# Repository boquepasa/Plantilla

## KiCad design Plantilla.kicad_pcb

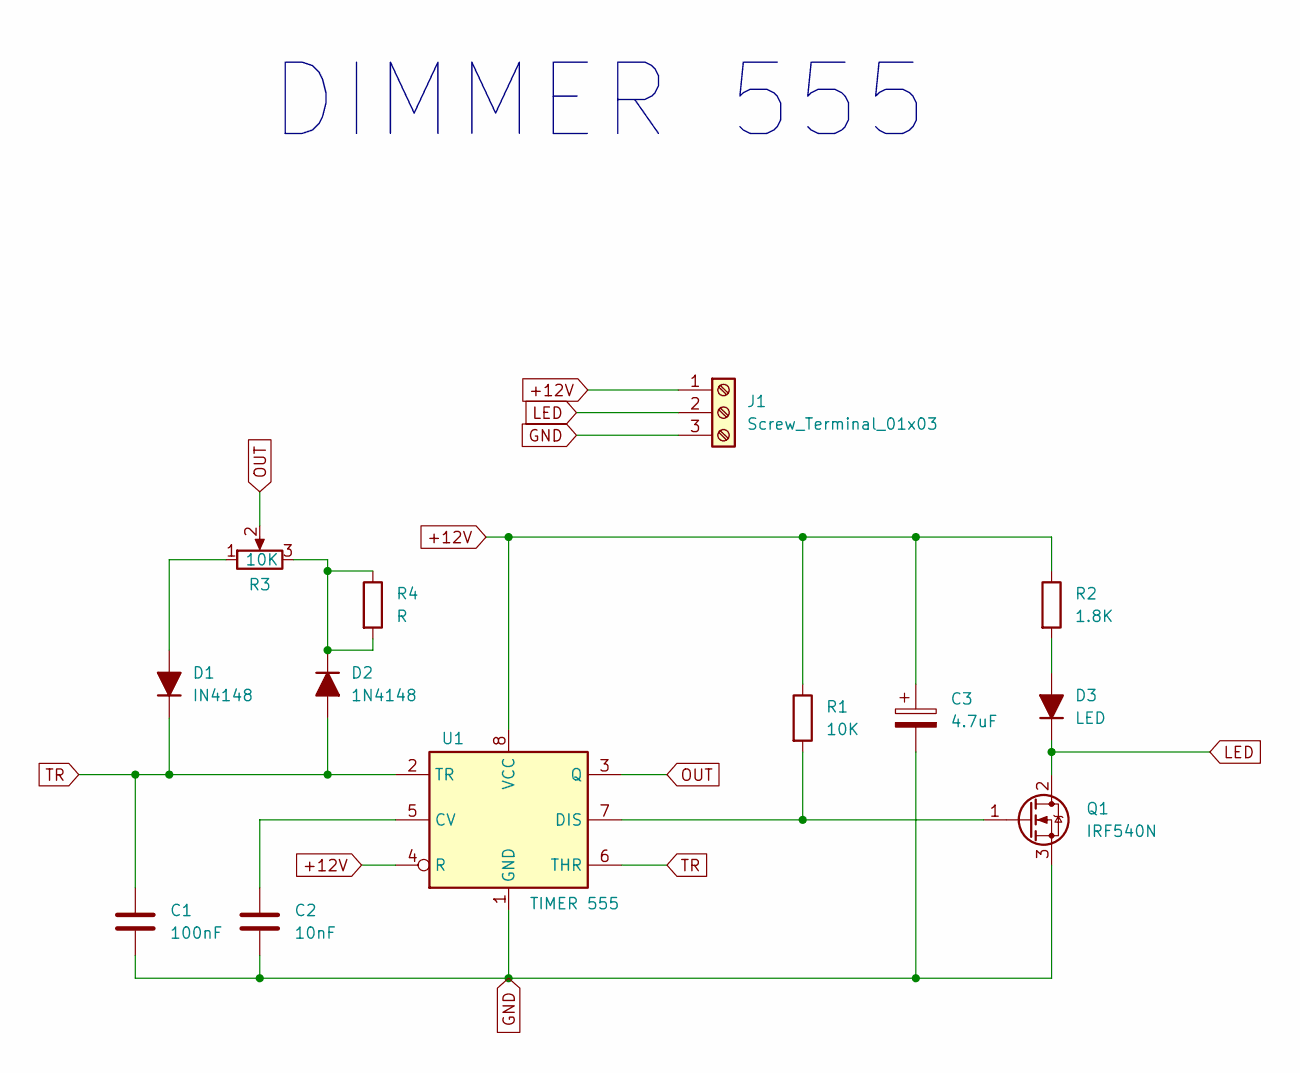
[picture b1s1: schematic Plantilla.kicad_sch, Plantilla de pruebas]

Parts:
C1: 100nF; C_0603_1608Metric
C2: 10nF; C_0603_1608Metric
C3: 4.7uF; CP_Radial_D8.0mm_P3.50mm
D1: IN4148; D_SOD-128
D2: 1N4148; D_SOD-128
D3: LED; D_1206_3216Metric
J1: Screw_Terminal_01x03; TerminalBlock_Phoenix_MKDS-1,5-3-5.08_1x03_P5.08mm_Horizont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
Q1: IRF540N; TO-220-3_Vertical
R1: 10K; R_0805_2012Metric
R2: 1.8K; R_0805_2012Metric
R3: 10K; Potentiometer_Bourns_3314G_Vertical
R4: R
U1: TIMER 555; SOIC-8_3.9x4.9mm_P1.27mm

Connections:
+12V: C3.1, J1.1, R1.1, R2.1, U1.4 (R), U1.8 (VCC)
GND: C1.2, C2.2, C3.2, J1.3, Q1.3 (S), U1.1 (GND)
LED: D3.1 (K), J1.2, Q1.2 (D)
unnamed: D1.2 (A), R3.1
unnamed: D2.1 (K), R3.3, R4.1, R4.2
unnamed: D3.2 (A), R2.2
unnamed: Q1.1 (G), R1.2, U1.7 (DIS)
unnamed: C2.1, U1.5 (CV)
OUT: R3.2, U1.3 (Q)
TR: C1.1, D1.1 (K), D2.2 (A), U1.2 (TR), U1.6 (THR)

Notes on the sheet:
DIMMER 555

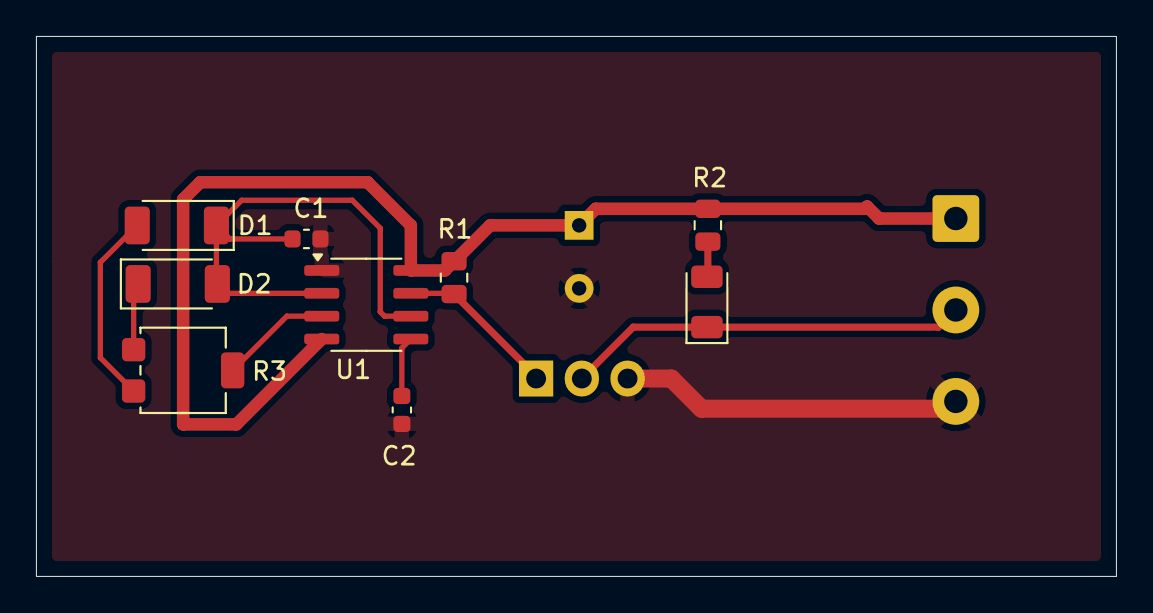
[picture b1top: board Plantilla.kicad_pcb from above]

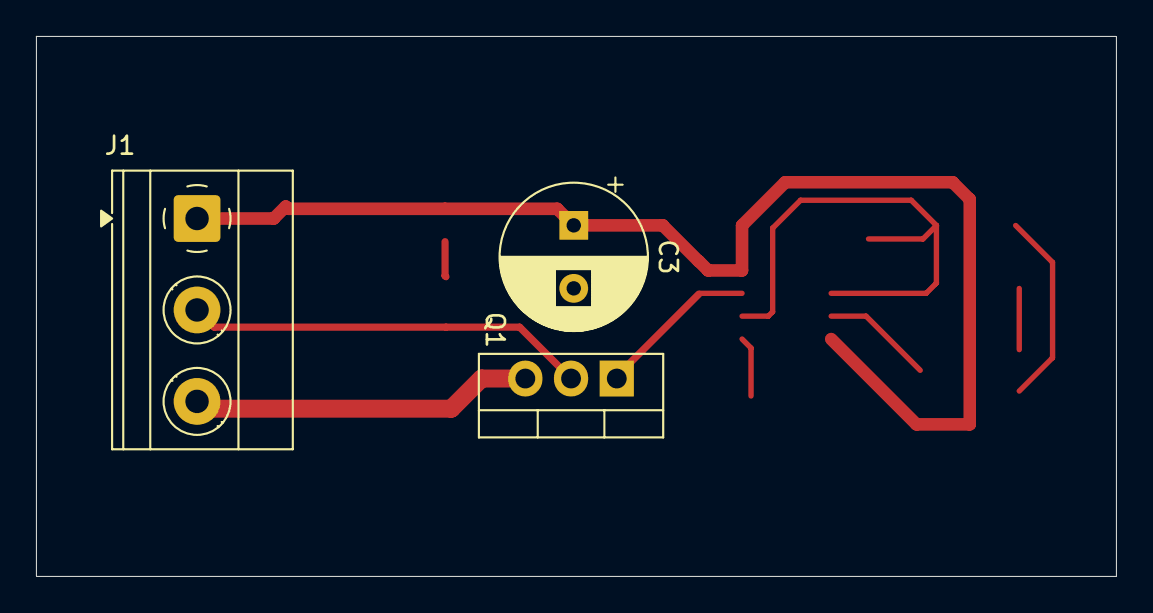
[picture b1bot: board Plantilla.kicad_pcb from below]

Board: 2 copper layers, 60.0 x 30.0 mm, 12 parts (3 on the bottom side), 10 nets.
